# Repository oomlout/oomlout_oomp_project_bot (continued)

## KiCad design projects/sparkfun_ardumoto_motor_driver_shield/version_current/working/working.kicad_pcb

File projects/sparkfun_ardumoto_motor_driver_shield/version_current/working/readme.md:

# OOMP Project  
## Ardumoto-Motor_Driver_Shield  by sparkfun  
  
oomp key: oomp_projects_flat_sparkfun_ardumoto_motor_driver_shield  
(snippet of original readme)  
  
SparkFun Ardumoto - Motor Driver Shield  
=======================================  

[*SparkFun Ardumoto - Motor Driver Shield (DEV-14129)*](https://www.sparkfun.com/products/14129)  
  
This is a motor shield for Arduino that will control two DC motors.   
Based on the L298 H-bridge, the SparkFun Ardumoto can drive up to 2 amps per channel.   
  
Repository Contents  
-------------------  
* **/Firmware** - Example Arduino sketch  
* **/Hardware** - All Eagle design files (.brd, .sch)  
  
Documentation  
--------------  
* [Hookup Guide](https://learn.sparkfun.com/tutorials/ardumoto-kit-hookup-guide)  
  
Version History  
---------------  
  
* [HW_1.4_FW_1.0](https://github.com/sparkfun/Ardumoto-Motor_Driver_Shield/tree/HW_1.4_FW_1.0) - Version 1.4  
* [V_2.0.0](https://github.com/sparkfun/Ardumoto-Motor_Driver_Shield/tree/V_2.0.0) - Initial build release  
* [V_2.0.1](https://github.com/sparkfun/Ardumoto-Motor_Driver_Shield/tree/V_2.0.1) - Public release  
  
License Information  
-------------------  
The hardware is released under [Creative Commons ShareAlike 4.0 International](https://creativecommons.org/licenses/by-sa/4.0/).  
The code is beerware; if you see me (or any other SparkFun employee) at the local, and you've found our code helpful, please buy us a round!  
  
Distributed as-is; no warranty is given.  
  
  full source readme at [readme_src.md](readme_src.md)  
  
source repo at: [https://github.com/sparkfun/Ardumoto-Motor_Driver_Shield](https://github.com/sparkfun/Ardumoto-Motor_Driver_Shield)  
## Board  

## Schematic  

[schematic pdf](working_schematic.pdf)  
## Images

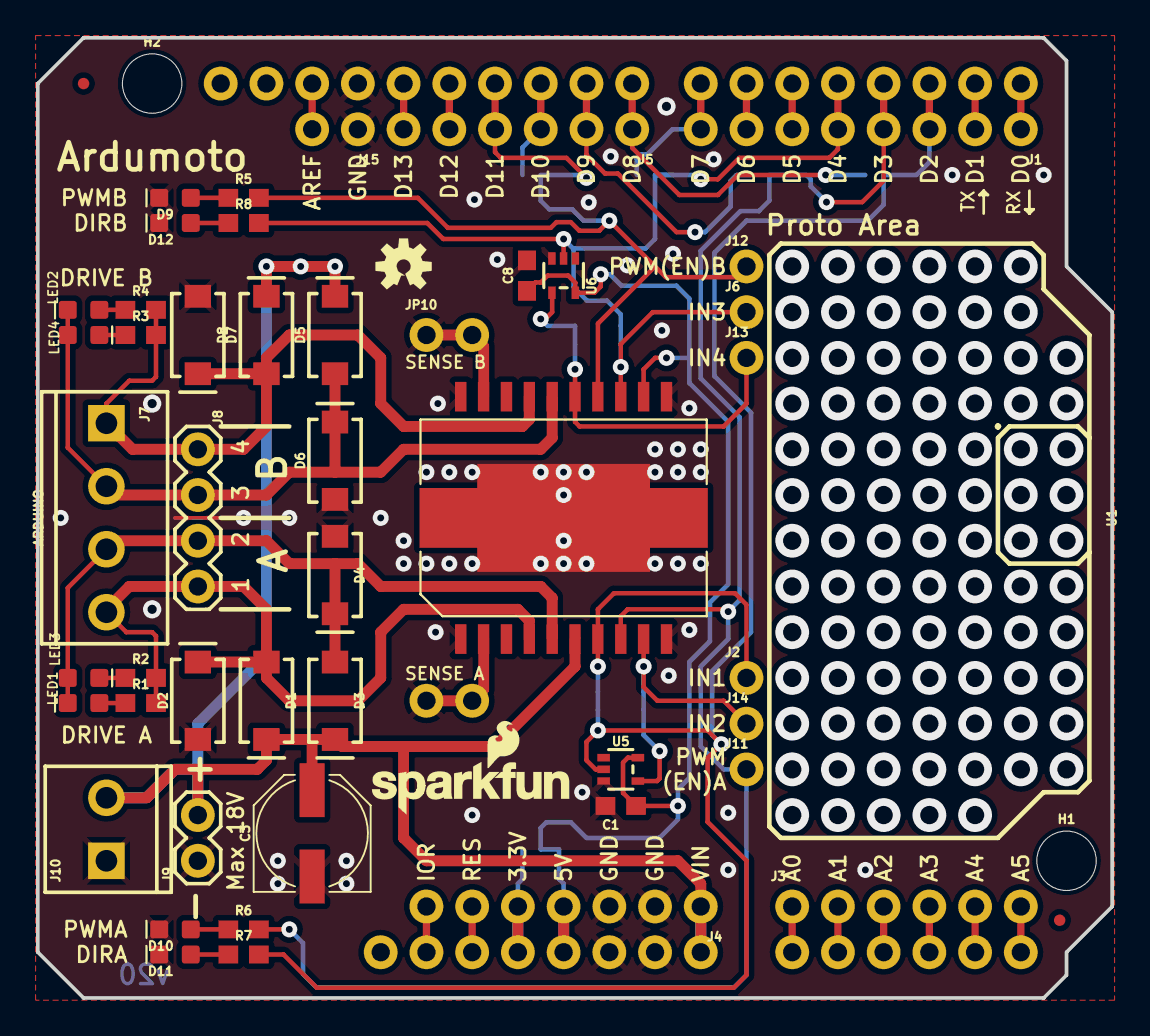
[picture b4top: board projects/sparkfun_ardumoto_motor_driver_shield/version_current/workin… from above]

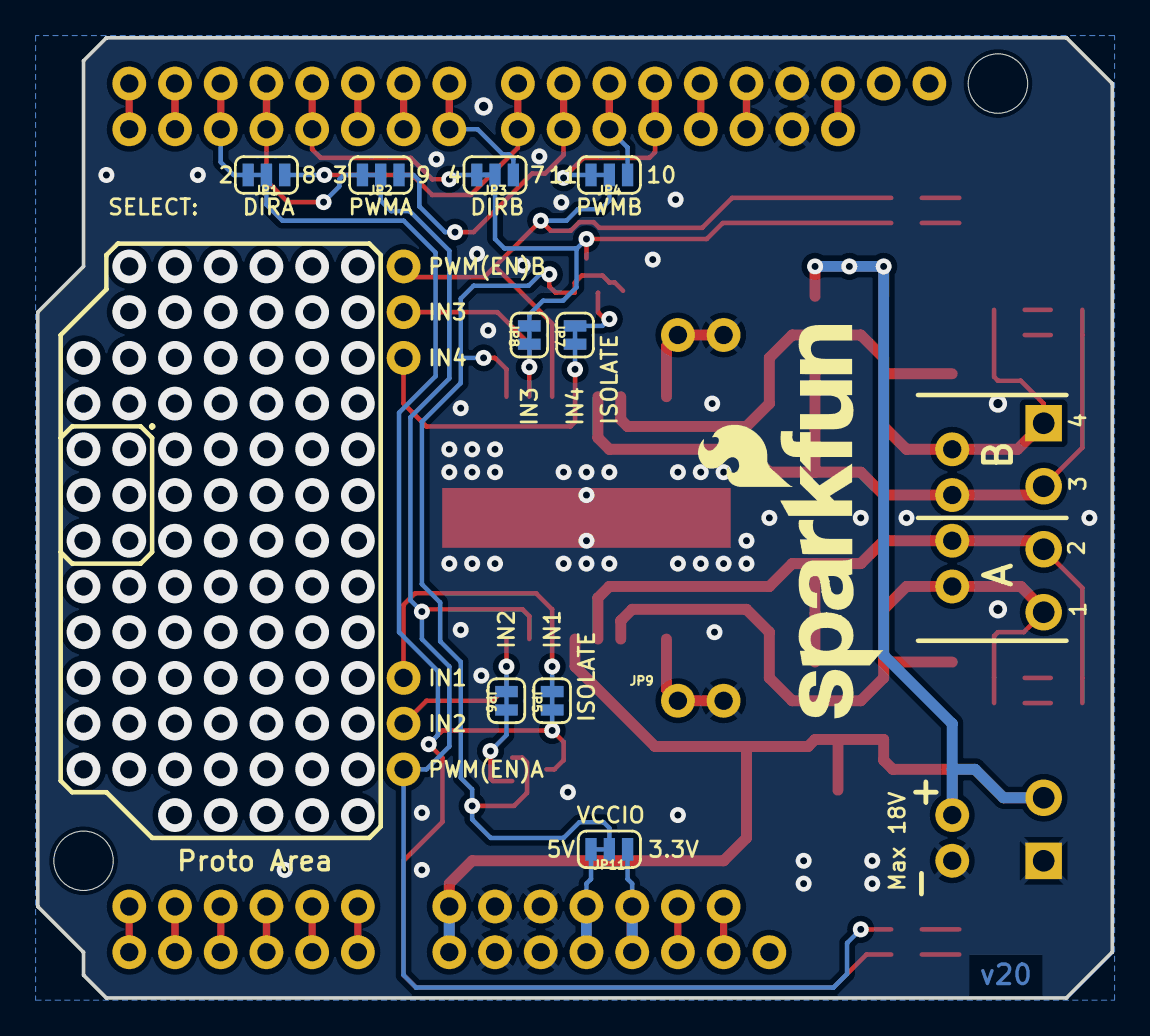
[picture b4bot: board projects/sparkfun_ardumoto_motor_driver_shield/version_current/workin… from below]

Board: 2 copper layers, 59.7 x 53.3 mm, 66 parts (11 on the bottom side), 52 nets.

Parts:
C1, C8: 0.1uF; 0603
C3: 100uF; PANASONIC_D
D1, D2, D3, D4, D5, D6, D7, D8: 1A/40V/500mV; SMA-DIODE
D9, D10, D11, D12: RED; LED-0603
FD1, FD2: FIDUCIALUFIDUCIAL; MICRO-FIDUCIAL
FRAME1: FRAME-LETTER; CREATIVE_COMMONS
FRAME2: FRAME-LETTERNO_PACKAGE; DUMMY
H1, H2: STAND-OFF
J1: 1X08_NO_SILK
J2, J6, J11, J12, J13, J14: 1X01_NO_SILK
J3, J5: 1X06_NO_SILK
J4: 1X07_NO_SILK
J7: SCREWTERMINAL-3.5MM-4
J8: 1X04
J9: 1X02
J10: SCREWTERMINAL-3.5MM-2
J15: 1X02_NO_SILK
JP1, JP2, JP3, JP4, JP11: 31NCT; SMT-JUMPER_3_1-NC_TRACE_SILK
JP5, JP6, JP7, JP8: 2NCT; SMT-JUMPER_2_NC_TRACE_SILK
JP9, JP10: 1X02_NO_SILK
LED1, LED4: BLUE; LED-0603
LED2, LED3: Yellow; LED-0603
LOGO1: SFE_LOGO_NAME_FLAME.2_INCH; SFE_LOGO_NAME_FLAME_.2
LOGO2: SFE_LOGO_NAME_FLAME.1_INCH; SFE_LOGO_NAME_FLAME_.1
R1, R2, R3, R4, R5, R6, R7, R8: 1k; 0603
U1: ARDUINO; UNO_R3_SHIELD_NOLABELS
U2: L298; POWERSO20_L298_PAD
U5, U6: 74HC1G04; SOT353
U$1: OSHW-LOGOS; OSHW-LOGO-S

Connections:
3.3V: J4.5, JP11.1, U1.3.3V
5V: J4.4, JP11.3, U1.5V
D0: J1.1, U1.RX
D1: J1.2, U1.TX
D2: J1.3, JP1.3, U1.D2
D3: J1.4, JP2.3, U1.D3
D4: J1.5, JP3.3, U1.D4
D5: J1.6, U1.D5
D6: J1.7, U1.D6
D7: J1.8, JP3.1, U1.D7
D8: J5.1, JP1.1, U1.D8
D9: J5.2, JP2.1, U1.D9
D10: J5.3, JP4.1, U1.D10
D11: J5.4, JP4.3, U1.D11
D12: J5.5, U1.D12
D13: J5.6, U1.D13
DIRA: JP1.2, JP5.1, R7.2, U5.2
DIRB: JP3.2, JP8.2, R8.2, U6.2
GND: C1.2, C3.-, C8.2, D2.A, D4.A, D6.A, D8.A, D9.C, D10.C, D11.C, D12.C, J4.2, J4.3, J9.1, J10.1, J15.1, JP9.2, JP10.1, U1.GND@0, U1.GND@1, U1.GND@2, U2.1, U2.10, U2.11, U2.20, U2.PAD, U5.3, U6.3
IN1: J2.1, JP5.2, U2.7
IN2: J14.1, JP6.2, U2.9
IN3: J6.1, JP8.1, U2.13
IN4: J13.1, JP7.1, U2.15
IOREF: J4.7, U1.IOREF
unnamed: LED1.A, R1.1
unnamed: LED3.C, R2.1
unnamed: LED4.C, R3.1
unnamed: LED2.A, R4.1
unnamed: J15.2, U1.AREF
unnamed: J3.1, U1.A0
unnamed: J3.2, U1.A1
unnamed: J3.3, U1.A2
unnamed: J3.4, U1.A3
unnamed: J3.5, U1.A4
unnamed: J3.6, U1.A5
unnamed: D9.A, R5.1
unnamed: D10.A, R6.1
unnamed: D12.A, R8.1
unnamed: D11.A, R7.1
NDIRA: JP6.1, U5.4
NDIRB: JP7.2, U6.4
OUT1: D1.A, D2.C, J7.4, J8.4, R1.2, R2.2, U2.4
OUT2: D3.A, D4.C, J7.3, J8.3, LED1.C, LED3.A, U2.5
OUT3: D5.A, D6.C, J7.2, J8.2, LED2.C, LED4.A, U2.16
OUT4: D7.A, D8.C, J7.1, J8.1, R3.2, R4.2, U2.17
PWMA: J11.1, JP2.2, R6.2, U2.8
PWMB: J12.1, JP4.2, R5.2, U2.14
RESET: J4.6, U1.RES
SENA: JP9.1, U2.2
SENB: JP10.2, U2.19
VCCIO: C1.1, C8.1, JP11.2, U2.12, U5.5, U6.5
VIN: C3.+, D1.C, D3.C, D5.C, D7.C, J4.1, J9.2, J10.2, U1.VIN, U2.6

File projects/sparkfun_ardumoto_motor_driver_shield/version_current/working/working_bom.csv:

"Id";"Designator";"Footprint";"Quantity";"Designation";"Supplier and ref";
1;"J15,JP10,JP9";"1X02_NO_SILK";3;"";;;
2;"D6,D5,D2,D1,D4,D3,D7,D8";"SMA-DIODE";8;"1A/40V/500mV";;;
3;"J4";"1X07_NO_SILK";1;"";;;
4;"R1,R5,R8,R6,R4,R3,R7,R2";"0603";8;"1k";;;
5;"J2,J6,J12,J11,J13,J14";"1X01_NO_SILK";6;"";;;
6;"J1";"1X08_NO_SILK";1;"";;;
7;"C8,C1";"0603";2;"0.1uF";;;
8;"H2,H1";"STAND-OFF";2;"STAND-OFF";;;
9;"C3";"PANASONIC_D";1;"100uF";;;
10;"D9,D11,D10,D12";"LED-0603";4;"RED";;;
11;"U5,U6";"SOT353";2;"74HC1G04";;;
12;"FRAME1";"CREATIVE_COMMONS";1;"FRAME-LETTER";;;
13;"J9";"1X02";1;"";;;
14;"FD2,FD1";"MICRO-FIDUCIAL";2;"FIDUCIALUFIDUCIAL";;;
15;"J5,J3";"1X06_NO_SILK";2;"";;;
16;"LED2,LED3";"LED-0603";2;"Yellow";;;
17;"J8";"1X04";1;"";;;
18;"U$1";"OSHW-LOGO-S";1;"OSHW-LOGOS";;;
19;"FRAME2";"DUMMY";1;"FRAME-LETTERNO_PACKAGE";;;
20;"J10";"SCREWTERMINAL-3.5MM-2";1;"";;;
21;"J7";"SCREWTERMINAL-3.5MM-4";1;"";;;
22;"U2";"POWERSO20_L298_PAD";1;"L298";;;
23;"LED1,LED4";"LED-0603";2;"BLUE";;;
24;"U1";"UNO_R3_SHIELD_NOLABELS";1;"ARDUINO";;;
25;"LOGO2";"SFE_LOGO_NAME_FLAME_.1";1;"SFE_LOGO_NAME_FLAME.1_INCH";;;
26;"LOGO1";"SFE_LOGO_NAME_FLAME_.2";1;"SFE_LOGO_NAME_FLAME.2_INCH";;;
27;"JP5,JP7,JP8,JP6";"SMT-JUMPER_2_NC_TRACE_SILK";4;"2NCT";;;
28;"JP1,JP11,JP3,JP2,JP4";"SMT-JUMPER_3_1-NC_TRACE_SILK";5;"31NCT";;;

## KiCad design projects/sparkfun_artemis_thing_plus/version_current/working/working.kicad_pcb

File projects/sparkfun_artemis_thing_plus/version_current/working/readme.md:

# Artemis_Thing_Plus by sparkfun  
This is a harvested standardized copy of a project from github.  
The original project can be found at:  
https://github.com/sparkfun/Artemis_Thing_Plus  
Please consult that link for additional, details, files, and license information.  
Note: It was auto harvested and if the original repo had more than one board file or anything out of the ordinary the files here are likely not representative.

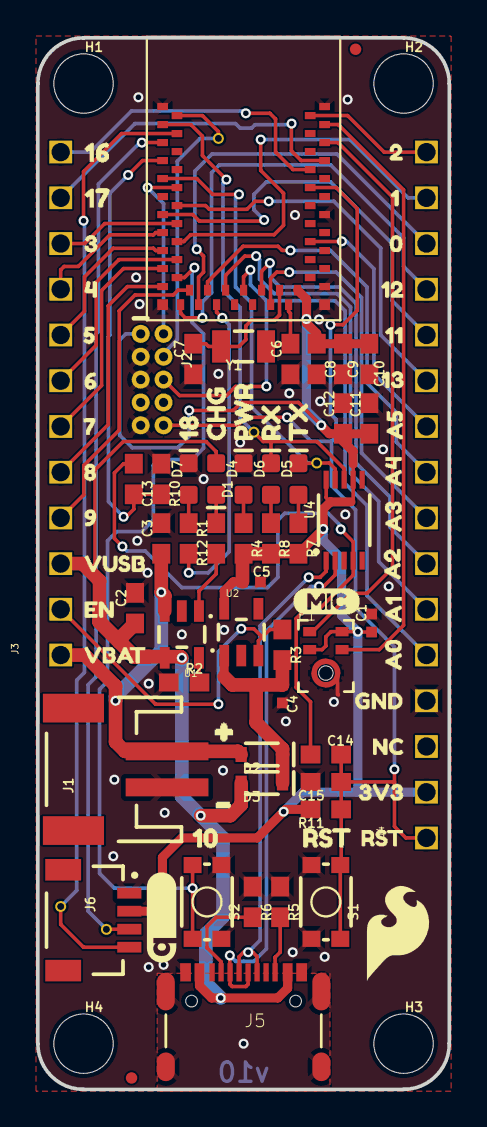
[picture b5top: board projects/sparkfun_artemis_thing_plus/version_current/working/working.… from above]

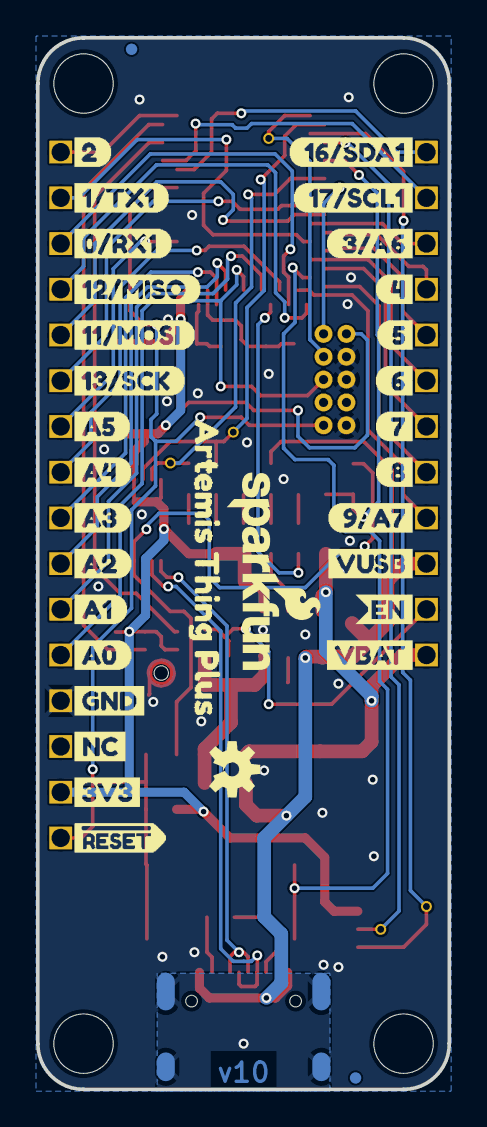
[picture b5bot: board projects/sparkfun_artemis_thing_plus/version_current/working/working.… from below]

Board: 4 copper layers, 22.9 x 58.4 mm, 133 parts (33 on the bottom side), 54 nets.

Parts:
C1: 0.1uF; 0402-TIGHT
C2, C3: 4.7uF; 0603
C4, C5: 1.0uF; 0402-TIGHT
C6, C7: 15pF; 0603
C8: 10uF; 0603
C9: 1.0uF; 0603
C10, C11, C13, C14: 0.1uF; 0603
C12: 10nF; 0603
C15: 1nF; 0603
D1, D6: Yellow; LED-0603
D2, D3: 3A/10V/280mV; SOD-323
D4: RED; LED-0603
D5: GREEN; LED-0603
D7: BLUE; LED-0603
E1: SPH0641LM4H; SPH0641LM4H-1_MICROPHONE
FD1, FD2, FD3, FD4: FIDUCIALUFIDUCIAL; FIDUCIAL-MICRO
FRAME1: FRAME-LETTER; CREATIVE_COMMONS
FRAME2: FRAME-LETTERNO_PACKAGE; DUMMY
H1, H2, H3, H4: STAND-OFF
J1: JST-2-SMD
J2: CORTEX_DEBUG; 2X5-PTH-1.27MM-NO_SILK
J3: 1X12_SM_SQ_NOSILK
J4: 1X16_SM_SQ_NOSILK
J5: USB-C; USB-C-16P
J6: JST04_1MM_RA
LOGO1: OSHW-LOGOS; OSHW-LOGO-S
LOGO2: QWIIC_LOGO_5MM; QWIIC_5MM
LOGO3: SFE_LOGO_NAME_FLAME.1_INCH; SFE_LOGO_NAME_FLAME_.1
R1, R4, R7, R8, R12: 1k; 0603
R2: 2.0k; 0603
R3: 10k; 0603
R5, R6: 5.1k; 0603
R10: 220k; 0603
R11: 100k; 0603
S1: RESET; TACTILE_SWITCH_SMD_4.6X2.8MM
S2: USER; TACTILE_SWITCH_SMD_4.6X2.8MM
TP1: TP_15TH
TP2, TP3, TP4, TP5: TEST-POINTTP_15TH_THRU; TP_15TH
U1: MCP73831; SOT23-5
U2: 3.3V; SOT23-5
U3: ARTEMIS_MODULESMD; ARTEMIS_FP
U4: CH340E_MSOP10; MSOP10
U$1: 160
U$2: 171
U$3: 32
U$4: 43
U$5: 54
U$6: 65
U$7: 76
U$8: 87
U$9: 98
U$10: VUSB9
U$11: EN10
U$12: VBAT11
U$13: 227
U$14: 126
U$15: 025
U$16: 1123
U$17: 1224
U$18: 1322
U$19: A521
U$20: A420
U$21: A319
U$22: A218
U$23: A117
U$24: A016
U$25: GND13
U$26: NC12
U$27, U$48: 3V314
U$28: RST15
U$29: 184
U$30: CHG1
U$31: PWR2
U$32: RX3
U$33: TX4
U$34: 20
U$35: 1#TX11
U$36: 0#RX12
U$37: 12#MISO3
U$38: 11#MOSI4
U$39: 13#SCK5
U$40: A56
U$41: A47
U$42: A38
U$43: A29
U$44: A110
U$45: A011
U$46: GND12
U$47: NC13
U$49: #RESET15
U$50: 16#SDA12
U$51: 17#SCL13
U$52: 412
U$53: 513
U$54: 614
U$55: 715
U$56: 816
U$57: 9#A719
U$58: 3#A60
U$59: VUSB25
U$60: EN26
U$61: VBAT27
U$62: 100
U$63: RST1
U$64: ARTEMIS_THING_PLUS0
U$65: SFE_LOGO_FLAME_.2
U$66: MIC0
U$67: #0
U$68: #1
Y1: 32.768kHz; CRYSTAL-SMD-3.2X1.5MM

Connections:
3.3V: C1.1, C5.1, C8.1, C9.1, C10.1, C11.1, C12.1, E1.2, E1.5, J2.1, J4.2, J6.2, R4.2, R7.2, R8.2, R11.2, U2.5, U3.VDD@36, U3.VDD@37, U4.7, U4.10
BOOT: C13.2, R10.2, U3.BOOT
CC1: J5.A5, R6.2
CC2: J5.B5, R5.2
D10/SWCH: S2.1, S2.2, U3.D14
D14/QWIIC_SDA: J6.3, TP5.P$1, U3.D40
D+1: J5.A6, J5.B6, U4.1
D-1: J5.A7, J5.B7, U4.2
EN: J3.2, R3.1, U2.3
GND: C1.2, C2.2, C3.2, C4.2, C5.2, C6.1, C7.1, C8.2, C9.2, C10.2, C11.2, C12.2, C15.2, D4.C, D7.C, E1.3, E1.6, E1.7, E1.8, J1.1, J2.3, J2.5, J2.9, J4.4, J5.GND, J5.GND2, J6.1, R2.1, R5.1, R6.1, R10.1, S1.1, S1.2, S2.3, S2.4, U1.2, U2.2, U3.GND@1, U3.GND@22, U3.GND@38, U3.GND@39, U3.GND@47, U3.GND@59, U4.3
unnamed: R2.2, U1.5
unnamed: C7.2, U3.XO, Y1.P$2
unnamed: D1.C, R1.2
unnamed: R1.1, U1.1
unnamed: D5.A, R7.1
unnamed: D7.A, R12.1
unnamed: C6.2, U3.XI, Y1.P$1
unnamed: D6.A, R8.1
unnamed: D4.A, R4.1
PDMCLK: E1.4, U3.~D37
PDMDATA: E1.1, U3.D36
RXI-0: D6.C, TP2.P$1, U3.RXI-0, U4.8
SHLD: J5.SHLD1, J5.SHLD2, J5.SHLD3, J5.SHLD4, J5.SHLD5, J5.SHLD6, J5.SHLD7, J5.SHLD8
SWDCK: J2.4, TP1.P$1, U3.SWDCK
SWDIO: J2.2, U3.SWDIO
TXO-0: D5.C, TP3.P$1, U3.TXO-0, U4.9
VIN: C4.1, D2.C, D3.C, R3.2, U2.1
V_BATT: C3.1, D2.A, J1.2, J3.1, U1.3
V_USB: C2.1, D1.A, D3.A, J3.3, J5.VBUS1, J5.VBUS2, U1.4
~D0/RXI-1: J4.14, U3.~D25
~D1/TXO-1: J4.15, U3.~D24
~D2: J4.16, U3.~D44
~D3/A6: J3.10, U3.~AD35
~D4: J3.9, U3.~D4
~D5: J3.8, U3.~D22
~D6: J3.7, U3.~D23
~D7: J3.6, U3.~D27
~D8: J3.5, U3.~D28
~D9/A7: J3.4, U3.~AD32
~D11/MOSI: J4.12, U3.D7
~D12/MISO: J4.13, U3.~D6
~D13/SCK: J4.11, U3.~D5
~D15/QWIIC_SCL: J6.4, TP4.P$1, U3.~D39
~D16/SDA1: J3.12, U3.~D43
~D17/SCL1: J3.11, U3.~D42
~D18/LED: R12.2, U3.~D26
~D19/A0: J2.6, J4.5, U3.~AD33/SWO
~D20/A1: J4.6, U3.~AD13
~D21/A2: J4.7, U3.~AD11
~D22/A3: J4.8, U3.~AD29
~D23/A4: J4.9, U3.~AD12
~D24/A5: J4.10, U3.~AD31
~RESET: C14.2, C15.1, J2.10, J4.1, R11.1, S1.3, S1.4, U3.~RST
~RTS: C13.1, C14.1, U4.4

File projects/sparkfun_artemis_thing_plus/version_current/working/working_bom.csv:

"Id";"Designator";"Footprint";"Quantity";"Designation";"Supplier and ref";
1;"U$65";"SFE_LOGO_FLAME_.2";1;"";;;
2;"U$14";"126";1;"";;;
3;"U$10";"VUSB9";1;"";;;
4;"D6,D1";"LED-0603";2;"Yellow";;;
5;"U$21";"A319";1;"";;;
6;"D2,D3";"SOD-323";2;"3A/10V/280mV";;;
7;"J2";"2X5-PTH-1.27MM-NO_SILK";1;"CORTEX_DEBUG";;;
8;"U3";"ARTEMIS_FP";1;"ARTEMIS_MODULESMD";;;
9;"H3,H1,H2,H4";"STAND-OFF";4;"STAND-OFF";;;
10;"U$13";"227";1;"";;;
11;"U$22";"A218";1;"";;;
12;"U$18";"1322";1;"";;;
13;"FD4,FD2,FD1,FD3";"FIDUCIAL-MICRO";4;"FIDUCIALUFIDUCIAL";;;
14;"U$27,U$48";"3V314";2;"";;;
15;"U$30";"CHG1";1;"";;;
16;"U$62";"100";1;"";;;
17;"U$12";"VBAT11";1;"";;;
18;"R2";"0603";1;"2.0k";;;
19;"U$26";"NC12";1;"";;;
20;"R8,R7,R4,R1,R12";"0603";5;"1k";;;
21;"U$11";"EN10";1;"";;;
22;"S1";"TACTILE_SWITCH_SMD_4.6X2.8MM";1;"RESET";;;
23;"R6,R5";"0603";2;"5.1k";;;
24;"U$63";"RST1";1;"";;;
25;"U1";"SOT23-5";1;"MCP73831";;;
26;"J5";"USB-C-16P";1;"USB-C";;;
27;"J3";"1X12_SM_SQ_NOSILK";1;"";;;
28;"U$20";"A420";1;"";;;
29;"J6";"JST04_1MM_RA";1;"";;;
30;"U$32";"RX3";1;"";;;
31;"C4,C5";"0402-TIGHT";2;"1.0uF";;;
32;"R3";"0603";1;"10k";;;
33;"TP5,TP3,TP4,TP2";"TP_15TH";4;"TEST-POINTTP_15TH_THRU";;;
34;"U$3";"32";1;"";;;
35;"C8";"0603";1;"10uF";;;
36;"C1";"0402-TIGHT";1;"0.1uF";;;
37;"U$68";"#1";1;"";;;
38;"U$8";"87";1;"";;;
39;"C10,C14,C11,C13";"0603";4;"0.1uF";;;
40;"U4";"MSOP10";1;"CH340E_MSOP10";;;
41;"C7,C6";"0603";2;"15pF";;;
42;"U$25";"GND13";1;"";;;
43;"U$6";"65";1;"";;;
44;"C12";"0603";1;"10nF";;;
45;"U$31";"PWR2";1;"";;;
46;"J4";"1X16_SM_SQ_NOSILK";1;"";;;
47;"U$2";"171";1;"";;;
48;"U$67";"#0";1;"";;;
49;"TP1";"TP_15TH";1;"";;;
50;"U$23";"A117";1;"";;;
51;"C15";"0603";1;"1nF";;;
52;"U$7";"76";1;"";;;
53;"R11";"0603";1;"100k";;;
54;"U$29";"184";1;"";;;
55;"U$24";"A016";1;"";;;
56;"U$15";"025";1;"";;;
57;"U$1";"160";1;"";;;
58;"FRAME2";"DUMMY";1;"FRAME-LETTERNO_PACKAGE";;;
59;"U$19";"A521";1;"";;;
60;"LOGO2";"QWIIC_5MM";1;"QWIIC_LOGO_5MM";;;
61;"Y1";"CRYSTAL-SMD-3.2X1.5MM";1;"32.768kHz";;;
62;"U$17";"1224";1;"";;;
63;"D7";"LED-0603";1;"BLUE";;;
64;"R10";"0603";1;"220k";;;
65;"U$33";"TX4";1;"";;;
66;"D4";"LED-0603";1;"RED";;;
67;"U2";"SOT23-5";1;"3.3V";;;
68;"U$9";"98";1;"";;;
69;"C9";"0603";1;"1.0uF";;;
70;"C3,C2";"0603";2;"4.7uF";;;
71;"U$28";"RST15";1;"";;;
72;"U$66";"MIC0";1;"";;;
73;"U$4";"43";1;"";;;
74;"D5";"LED-0603";1;"GREEN";;;
75;"E1";"SPH0641LM4H-1_MICROPHONE";1;"SPH0641LM4H";;;
76;"U$16";"1123";1;"";;;
77;"FRAME1";"CREATIVE_COMMONS";1;"FRAME-LETTER";;;
78;"J1";"JST-2-SMD";1;"";;;
79;"U$5";"54";1;"";;;
80;"S2";"TACTILE_SWITCH_SMD_4.6X2.8MM";1;"USER";;;
81;"U$47";"NC13";1;"";;;
82;"U$38";"11#MOSI4";1;"";;;
83;"U$45";"A011";1;"";;;
84;"U$60";"EN26";1;"";;;
85;"U$36";"0#RX12";1;"";;;
86;"U$42";"A38";1;"";;;
87;"U$34";"20";1;"";;;
88;"U$56";"816";1;"";;;
89;"U$58";"3#A60";1;"";;;
90;"U$53";"513";1;"";;;
91;"U$64";"ARTEMIS_THING_PLUS0";1;"";;;
92;"U$44";"A110";1;"";;;
93;"U$61";"VBAT27";1;"";;;
94;"U$40";"A56";1;"";;;
95;"U$50";"16#SDA12";1;"";;;
96;"U$41";"A47";1;"";;;
97;"U$52";"412";1;"";;;
98;"LOGO1";"OSHW-LOGO-S";1;"OSHW-LOGOS";;;
99;"U$51";"17#SCL13";1;"";;;
100;"U$39";"13#SCK5";1;"";;;
101;"U$49";"#RESET15";1;"";;;
102;"U$43";"A29";1;"";;;
103;"U$57";"9#A719";1;"";;;
104;"U$37";"12#MISO3";1;"";;;
105;"U$54";"614";1;"";;;
106;"U$55";"715";1;"";;;
107;"LOGO3";"SFE_LOGO_NAME_FLAME_.1";1;"SFE_LOGO_NAME_FLAME.1_INCH";;;
108;"U$35";"1#TX11";1;"";;;
109;"U$59";"VUSB25";1;"";;;
110;"U$46";"GND12";1;"";;;

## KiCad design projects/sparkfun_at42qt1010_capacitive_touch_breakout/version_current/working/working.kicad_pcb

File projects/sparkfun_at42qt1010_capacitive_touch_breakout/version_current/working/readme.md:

# AT42QT1010_Capacitive_Touch_Breakout by sparkfun  
This is a harvested standardized copy of a project from github.  
The original project can be found at:  
https://github.com/sparkfun/AT42QT1010_Capacitive_Touch_Breakout  
Please consult that link for additional, details, files, and license information.  
Note: It was auto harvested and if the original repo had more than one board file or anything out of the ordinary the files here are likely not representative.

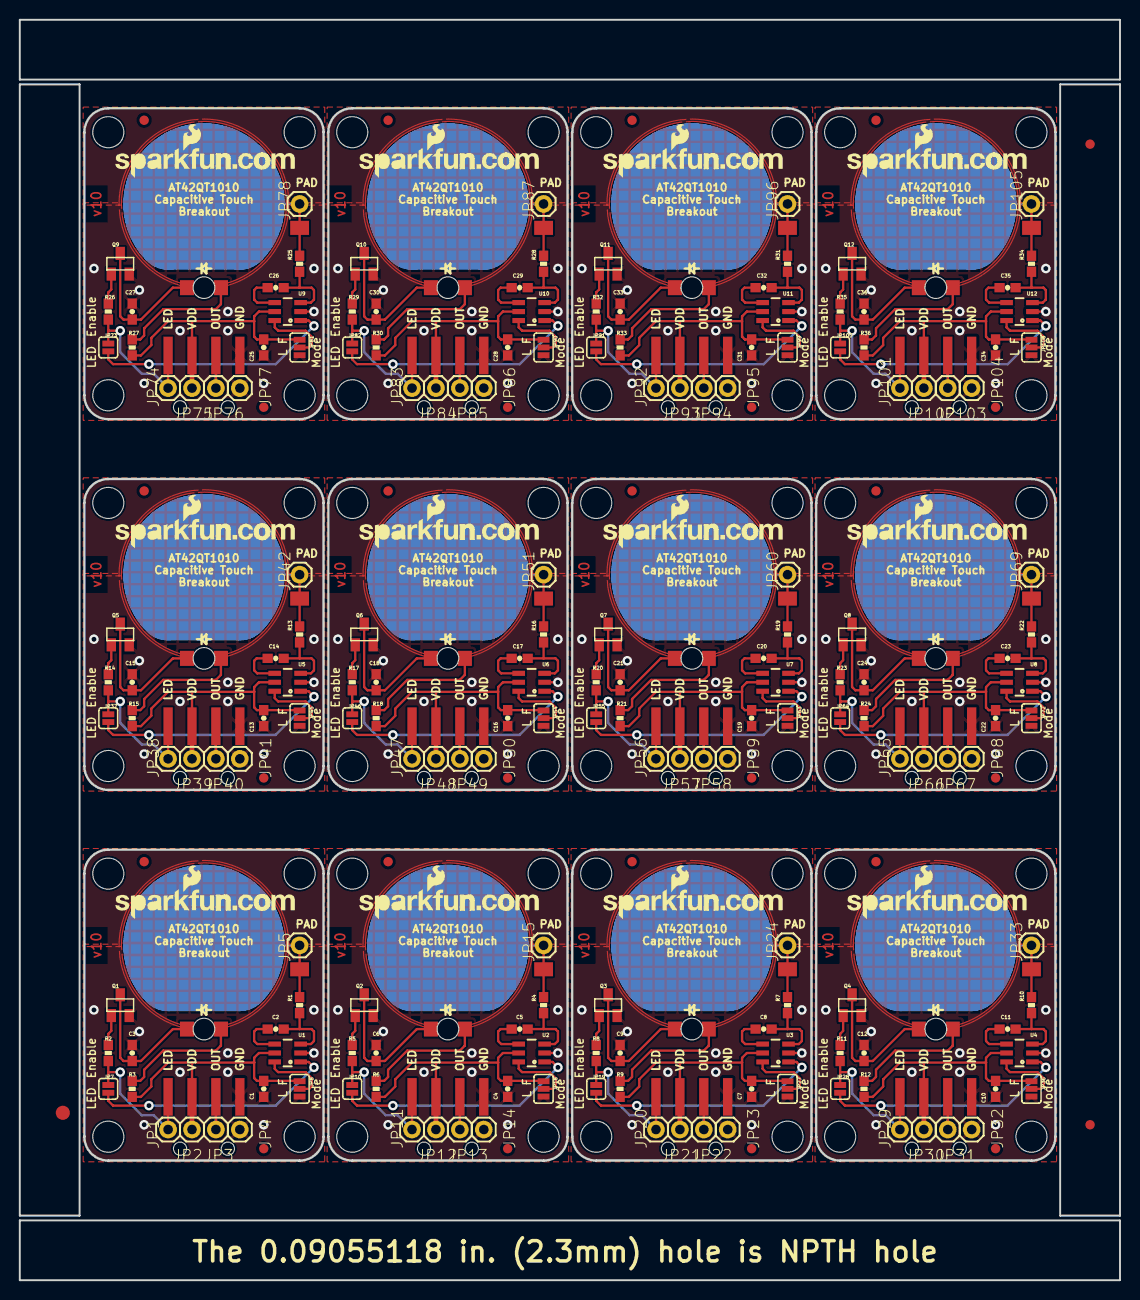
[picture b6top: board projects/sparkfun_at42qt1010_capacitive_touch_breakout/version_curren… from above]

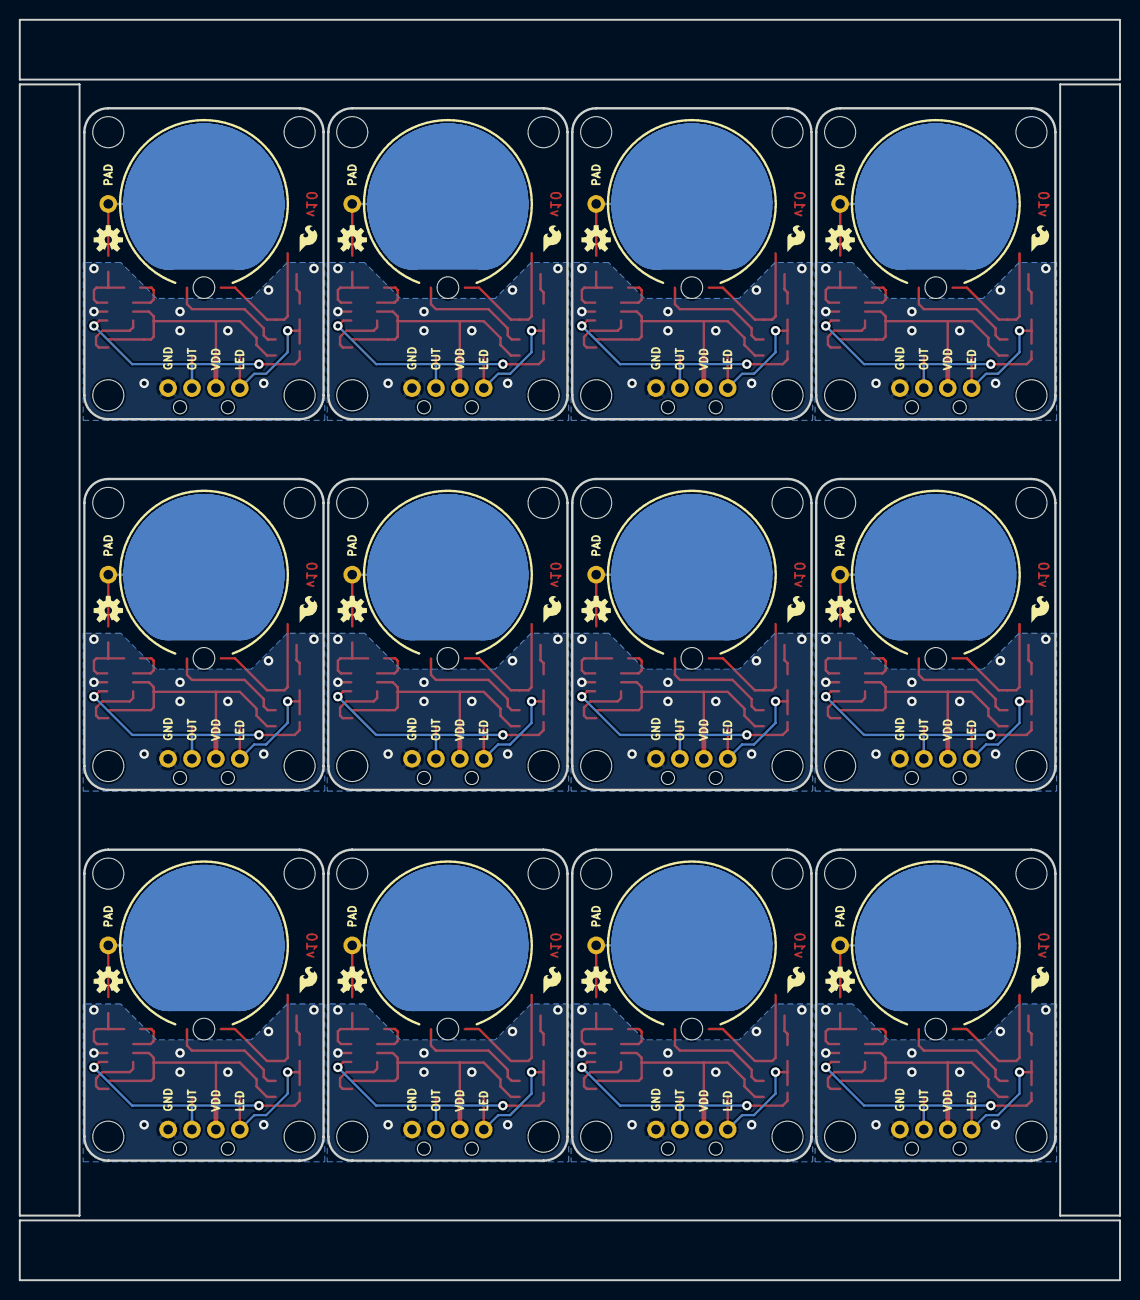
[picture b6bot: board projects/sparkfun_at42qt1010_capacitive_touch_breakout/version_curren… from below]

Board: 4 copper layers, 116.8 x 133.9 mm, 327 parts (24 on the bottom side), 132 nets.

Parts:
C1, C4, C7, C10, C13, C16, C19, C22, C25, C28, C31, C34: 0.1uF; 0603-CAP
C2, C3, C5, C6, C8, C9, C11, C12, C14, C15, C17, C18, C20, C21, C23, C24, C26, C27, C29, C30, C32, C33, C35, C36: 10nF; 0603-CAP
E$1: FIDUCIAL-1.5X3
E$4, E$5: FIDUCIAL-1X2
FID1, FID2, FID3, FID4, FID5, FID6, FID7, FID8, FID9, FID10, FID11, FID12, FID13, FID14, FID15, FID16, FID17, FID18, FID19, FID20, FID21, FID22, FID23, FID24: FIDUCIAL1X2; FIDUCIAL-1X2
JP1, JP2, JP3, JP4, JP5, JP11, JP12, JP13, JP14, JP15, JP20, JP21, JP22, JP23, JP24, JP29, JP30, JP31, JP32, JP33, JP38, JP39, JP40, JP41, JP42, JP47, JP48, JP49, JP50, JP51, JP56, JP57, JP58, JP59, JP60, JP65, JP66, JP67, JP68, JP69, JP74, JP75, JP76, JP77, JP78, JP83, JP84, JP85, JP86, JP87, JP92, JP93, JP94, JP95, JP96, JP101, JP102, JP103, JP104, JP105: M01PTH; 1X01
JP6, JP16, JP25, JP34, JP43, JP52, JP61, JP70, JP79, JP88, JP97, JP106: SMD; 1X04-SMD_LONG
JP7, JP10, JP19, JP28, JP37, JP46, JP55, JP64, JP73, JP82, JP91, JP100: NC; SJ_2S
JP8, JP18, JP27, JP36, JP45, JP54, JP63, JP72, JP81, JP90, JP99, JP108: JUMPER-31-2; SJ_3_PASTE1&2
JP9, JP17, JP26, JP35, JP44, JP53, JP62, JP71, JP80, JP89, JP98, JP107: M01SMD-4.5X1.5; PAD-1.5X4.5
LED1, LED2, LED3, LED4, LED5, LED6, LED7, LED8, LED9, LED10, LED11, LED12: GREEN; LED-1206-BOTTOM
LOGO1, LOGO5, LOGO8, LOGO11, LOGO14, LOGO17, LOGO20, LOGO23, LOGO26, LOGO29, LOGO32, LOGO35: LOGO-SFENEW; SFE-NEW-WEBLOGO
LOGO2, LOGO4, LOGO7, LOGO10, LOGO13, LOGO16, LOGO19, LOGO22, LOGO25, LOGO28, LOGO31, LOGO34: OSHW-LOGOS; OSHW-LOGO-S
LOGO3, LOGO6, LOGO9, LOGO12, LOGO15, LOGO18, LOGO21, LOGO24, LOGO27, LOGO30, LOGO33, LOGO36: LOGO-SFESK; SFE-LOGO-FLAME
Q1, Q2, Q3, Q4, Q5, Q6, Q7, Q8, Q9, Q10, Q11, Q12: NPN; SOT23
R1, R4, R7, R10, R13, R16, R19, R22, R25, R28, R31, R34: 10k; 0603-RES
R2, R5, R8, R11, R14, R17, R20, R23, R26, R29, R32, R35: 2.2k; 0603-RES
R3, R6, R9, R12, R15, R18, R21, R24, R27, R30, R33, R36: 200; 0603-RES
STANDOFF1, STANDOFF2, STANDOFF3, STANDOFF4, STANDOFF5, STANDOFF6, STANDOFF7, STANDOFF8, STANDOFF9, STANDOFF10, STANDOFF11, STANDOFF12, STANDOFF13, STANDOFF14, STANDOFF15, STANDOFF16, STANDOFF17, STANDOFF18, STANDOFF19, STANDOFF20, STANDOFF21, STANDOFF22, STANDOFF23, STANDOFF24, STANDOFF25, STANDOFF26, STANDOFF27, STANDOFF28, STANDOFF29, STANDOFF30, STANDOFF31, STANDOFF32, STANDOFF33, STANDOFF34, STANDOFF35, STANDOFF36, STANDOFF37, STANDOFF38, STANDOFF39, STANDOFF40, STANDOFF41, STANDOFF42, STANDOFF43, STANDOFF44, STANDOFF45, STANDOFF46, STANDOFF47, STANDOFF48: STAND-OFF
U1, U2, U3, U4, U5, U6, U7, U8, U9, U10, U11, U12: AT42QT1010SOT23; SOT23-6

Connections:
GND: C1.2, C3.2, JP4.1, JP6.4, JP8.3, Q1.2, U1.2
GND1: C4.2, C6.2, JP14.1, JP16.4, JP18.3, Q2.2, U2.2
GND2: C7.2, C9.2, JP23.1, JP25.4, JP27.3, Q3.2, U3.2
GND3: C10.2, C12.2, JP32.1, JP34.4, JP36.3, Q4.2, U4.2
GND4: C13.2, C15.2, JP41.1, JP43.4, JP45.3, Q5.2, U5.2
GND5: C16.2, C18.2, JP50.1, JP52.4, JP54.3, Q6.2, U6.2
GND6: C19.2, C21.2, JP59.1, JP61.4, JP63.3, Q7.2, U7.2
GND7: C22.2, C24.2, JP68.1, JP70.4, JP72.3, Q8.2, U8.2
GND8: C25.2, C27.2, JP77.1, JP79.4, JP81.3, Q9.2, U9.2
GND9: C28.2, C30.2, JP86.1, JP88.4, JP90.3, Q10.2, U10.2
GND10: C31.2, C33.2, JP95.1, JP97.4, JP99.3, Q11.2, U11.2
GND11: C34.2, C36.2, JP104.1, JP106.4, JP108.3, Q12.2, U12.2
LED: JP1.1, JP6.1, JP7.2, R2.1
LED1: JP10.2, JP11.1, JP16.1, R5.1
LED2: JP19.2, JP20.1, JP25.1, R8.1
LED3: JP28.2, JP29.1, JP34.1, R11.1
LED4: JP37.2, JP38.1, JP43.1, R14.1
LED5: JP46.2, JP47.1, JP52.1, R17.1
LED6: JP55.2, JP56.1, JP61.1, R20.1
LED7: JP64.2, JP65.1, JP70.1, R23.1
LED8: JP73.2, JP74.1, JP79.1, R26.1
LED9: JP82.2, JP83.1, JP88.1, R29.1
LED10: JP91.2, JP92.1, JP97.1, R32.1
LED11: JP100.2, JP101.1, JP106.1, R35.1
unnamed: C5.2, U2.4
unnamed: C5.1, R4.1, U2.3
unnamed: JP18.2, U2.6
unnamed: C2.2, U1.4
unnamed: C2.1, R1.1, U1.3
unnamed: Q2.1, R5.2
unnamed: JP8.2, U1.6
unnamed: C6.1, LED2.C, Q2.3
unnamed: LED2.A, R6.1
unnamed: Q1.1, R2.2
unnamed: C3.1, LED1.C, Q1.3
unnamed: LED1.A, R3.1
unnamed: C8.2, U3.4
unnamed: C8.1, R7.1, U3.3
unnamed: JP27.2, U3.6
unnamed: Q3.1, R8.2
unnamed: C9.1, LED3.C, Q3.3
unnamed: LED3.A, R9.1
unnamed: C11.2, U4.4
unnamed: C11.1, R10.1, U4.3
unnamed: JP36.2, U4.6
unnamed: Q4.1, R11.2
unnamed: C12.1, LED4.C, Q4.3
unnamed: LED4.A, R12.1
unnamed: C14.2, U5.4
unnamed: C14.1, R13.1, U5.3
unnamed: JP45.2, U5.6
unnamed: Q5.1, R14.2
unnamed: C15.1, LED5.C, Q5.3
unnamed: LED5.A, R15.1
unnamed: C17.2, U6.4
unnamed: C17.1, R16.1, U6.3
unnamed: JP54.2, U6.6
unnamed: Q6.1, R17.2
unnamed: C18.1, LED6.C, Q6.3
unnamed: LED6.A, R18.1
unnamed: C20.2, U7.4
unnamed: C20.1, R19.1, U7.3
unnamed: JP63.2, U7.6
unnamed: Q7.1, R20.2
unnamed: C21.1, LED7.C, Q7.3
unnamed: LED7.A, R21.1
unnamed: C23.2, U8.4
unnamed: C23.1, R22.1, U8.3
unnamed: JP72.2, U8.6
unnamed: Q8.1, R23.2
unnamed: C24.1, LED8.C, Q8.3
unnamed: LED8.A, R24.1
unnamed: C26.2, U9.4
unnamed: C26.1, R25.1, U9.3
unnamed: JP81.2, U9.6
unnamed: Q9.1, R26.2
unnamed: C27.1, LED9.C, Q9.3
unnamed: LED9.A, R27.1
unnamed: C29.2, U10.4
unnamed: C29.1, R28.1, U10.3
unnamed: JP90.2, U10.6
unnamed: Q10.1, R29.2
unnamed: C30.1, LED10.C, Q10.3
unnamed: LED10.A, R30.1
unnamed: C32.2, U11.4
unnamed: C32.1, R31.1, U11.3
unnamed: JP99.2, U11.6
unnamed: Q11.1, R32.2
unnamed: C33.1, LED11.C, Q11.3
unnamed: LED11.A, R33.1
unnamed: C35.2, U12.4
unnamed: C35.1, R34.1, U12.3
unnamed: JP108.2, U12.6
unnamed: Q12.1, R35.2
unnamed: C36.1, LED12.C, Q12.3
unnamed: LED12.A, R36.1
OUT: JP3.1, JP6.3, JP7.1, U1.1
OUT1: JP10.1, JP13.1, JP16.3, U2.1
OUT2: JP19.1, JP22.1, JP25.3, U3.1
OUT3: JP28.1, JP31.1, JP34.3, U4.1
OUT4: JP37.1, JP40.1, JP43.3, U5.1
OUT5: JP46.1, JP49.1, JP52.3, U6.1
OUT6: JP55.1, JP58.1, JP61.3, U7.1
OUT7: JP64.1, JP67.1, JP70.3, U8.1
OUT8: JP73.1, JP76.1, JP79.3, U9.1
OUT9: JP82.1, JP85.1, JP88.3, U10.1
OUT10: JP91.1, JP94.1, JP97.3, U11.1
OUT11: JP100.1, JP103.1, JP106.3, U12.1
PAD: JP5.1, JP9.P$1, R1.2
PAD1: JP15.1, JP17.P$1, R4.2
PAD2: JP24.1, JP26.P$1, R7.2
PAD3: JP33.1, JP35.P$1, R10.2
PAD4: JP42.1, JP44.P$1, R13.2
PAD5: JP51.1, JP53.P$1, R16.2
PAD6: JP60.1, JP62.P$1, R19.2
PAD7: JP69.1, JP71.P$1, R22.2
PAD8: JP78.1, JP80.P$1, R25.2
PAD9: JP87.1, JP89.P$1, R28.2
PAD10: JP96.1, JP98.P$1, R31.2
PAD11: JP105.1, JP107.P$1, R34.2
VCC: C1.1, JP2.1, JP6.2, JP8.1, R3.2, U1.5
VCC1: C4.1, JP12.1, JP16.2, JP18.1, R6.2, U2.5
VCC2: C7.1, JP21.1, JP25.2, JP27.1, R9.2, U3.5
VCC3: C10.1, JP30.1, JP34.2, JP36.1, R12.2, U4.5
VCC4: C13.1, JP39.1, JP43.2, JP45.1, R15.2, U5.5
VCC5: C16.1, JP48.1, JP52.2, JP54.1, R18.2, U6.5
VCC6: C19.1, JP57.1, JP61.2, JP63.1, R21.2, U7.5
VCC7: C22.1, JP66.1, JP70.2, JP72.1, R24.2, U8.5
VCC8: C25.1, JP75.1, JP79.2, JP81.1, R27.2, U9.5
VCC9: C28.1, JP84.1, JP88.2, JP90.1, R30.2, U10.5
VCC10: C31.1, JP93.1, JP97.2, JP99.1, R33.2, U11.5
VCC11: C34.1, JP102.1, JP106.2, JP108.1, R36.2, U12.5

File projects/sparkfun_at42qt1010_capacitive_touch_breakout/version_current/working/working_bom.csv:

"Id";"Designator";"Footprint";"Quantity";"Designation";"Supplier and ref";
1;"STANDOFF33,STANDOFF47,STANDOFF27,STANDOFF25,STANDOFF2,STANDOFF37,STANDOFF30,STANDOFF21,STANDOFF48,STANDOFF13,STANDOFF18,STANDOFF3,STANDOFF15,STANDOFF23,STANDOFF43,STANDOFF46,STANDOFF35,STANDOFF6,STANDOFF45,STANDOFF24,STANDOFF10,STANDOFF40,STANDOFF5,STANDOFF14,STANDOFF19,STANDOFF39,STANDOFF12,STANDOFF4,STANDOFF29,STANDOFF31,STANDOFF44,STANDOFF28,STANDOFF11,STANDOFF8,STANDOFF16,STANDOFF34,STANDOFF36,STANDOFF9,STANDOFF20,STANDOFF42,STANDOFF41,STANDOFF7,STANDOFF1,STANDOFF17,STANDOFF26,STANDOFF22,STANDOFF32,STANDOFF38";"STAND-OFF";48;"STAND-OFF";;;
2;"JP13,JP33,JP49,JP5,JP58,JP48,JP68,JP51,JP93,JP56,JP101,JP83,JP84,JP94,JP1,JP4,JP12,JP2,JP103,JP24,JP95,JP31,JP42,JP23,JP21,JP57,JP96,JP41,JP69,JP14,JP32,JP85,JP87,JP59,JP74,JP3,JP75,JP76,JP104,JP30,JP38,JP65,JP60,JP29,JP66,JP78,JP67,JP105,JP22,JP86,JP92,JP77,JP11,JP20,JP40,JP47,JP15,JP50,JP39,JP102";"1X01";60;"M01PTH";;;
3;"JP9,JP107,JP80,JP26,JP71,JP17,JP44,JP53,JP89,JP98,JP62,JP35";"PAD-1.5X4.5";12;"M01SMD-4.5X1.5";;;
4;"JP97,JP6,JP43,JP25,JP70,JP52,JP106,JP16,JP88,JP34,JP61,JP79";"1X04-SMD_LONG";12;"SMD";;;
5;"U2,U8,U9,U11,U7,U1,U5,U3,U10,U6,U12,U4";"SOT23-6";12;"AT42QT1010SOT23";;;
6;"R26,R23,R29,R17,R32,R11,R14,R8,R2,R5,R20,R35";"0603-RES";12;"2.2k";;;
7;"C12,C9,C24,C35,C3,C36,C2,C32,C21,C33,C23,C6,C26,C15,C17,C18,C27,C5,C8,C14,C30,C11,C29,C20";"0603-CAP";24;"10nF";;;
8;"FID2,FID10,FID12,FID24,FID7,FID17,FID9,FID18,FID5,FID3,FID14,FID11,FID15,FID6,FID22,FID13,FID1,FID16,FID4,FID19,FID23,FID21,FID8,FID20";"FIDUCIAL-1X2";24;"FIDUCIAL1X2";;;
9;"JP99,JP72,JP27,JP81,JP18,JP108,JP90,JP8,JP36,JP54,JP63,JP45";"SJ_3_PASTE1&2";12;"JUMPER-31-2";;;
10;"C19,C25,C10,C28,C4,C7,C16,C34,C13,C1,C22,C31";"0603-CAP";12;"0.1uF";;;
11;"R4,R13,R34,R22,R1,R10,R16,R31,R19,R7,R25,R28";"0603-RES";12;"10k";;;
12;"LOGO26,LOGO5,LOGO14,LOGO35,LOGO23,LOGO1,LOGO17,LOGO20,LOGO32,LOGO11,LOGO29,LOGO8";"SFE-NEW-WEBLOGO";12;"LOGO-SFENEW";;;
13;"R3,R24,R36,R18,R33,R12,R30,R21,R27,R9,R15,R6";"0603-RES";12;"200";;;
14;"LED11,LED12,LED7,LED6,LED2,LED9,LED4,LED10,LED3,LED5,LED8,LED1";"LED-1206-BOTTOM";12;"GREEN";;;
15;"Q11,Q4,Q9,Q6,Q5,Q8,Q2,Q7,Q10,Q1,Q3,Q12";"SOT23";12;"NPN";;;
16;"JP64,JP19,JP37,JP10,JP73,JP7,JP100,JP46,JP55,JP91,JP82,JP28";"SJ_2S";12;"NC";;;
17;"E$5,E$4";"FIDUCIAL-1X2";2;"";;;
18;"E$1";"FIDUCIAL-1.5X3";1;"";;;
19;"LOGO24,LOGO33,LOGO15,LOGO27,LOGO12,LOGO18,LOGO9,LOGO30,LOGO36,LOGO3,LOGO21,LOGO6";"SFE-LOGO-FLAME";12;"LOGO-SFESK";;;
20;"LOGO7,LOGO10,LOGO19,LOGO4,LOGO16,LOGO28,LOGO25,LOGO2,LOGO22,LOGO13,LOGO31,LOGO34";"OSHW-LOGO-S";12;"OSHW-LOGOS";;;
